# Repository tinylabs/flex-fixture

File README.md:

## flex-fixture
Oscilloscope fixture to ease in simple probing without causing undue mess on the workspace. It allows me to more quickly switch between projects and to clean up after by moving the probe boom out of the way. In addition each probe can be plugged directly into Saleae Pro 8 for logic analysis.

### COTS Components
* [Boom microphone mount](https://www.amazon.com/gp/product/B07V2FJL54/ref=ppx_yo_dt_b_asin_title_o07_s00?ie=UTF8&psc=1)
* [5/8 to 3/8" adapter](https://www.amazon.com/Donuts-Adapter-Female-Knurled-Microphone/dp/B08VGTCZWN)
* [Magnetic mount PCB holder + flex arms](https://www.aliexpress.us/item/2251832832414460.html)
* [P100 pogo pins](https://www.amazon.com/gp/product/B017N4Y79U)
* [P100 pogo pins](https://www.amazon.com/gp/product/B018HMJKRG)
* [P100 pogo pin receptacle](https://www.amazon.com/Spring-Probe-Sleeve-Accessory-R125%E2%80%914s/dp/B0B6PNLFZ7)
* [CONBNC002](https://www.mouser.com/ProductDetail/Linx-Technologies/CONBNC002)
* Probe to BNC adapter (typically included with oscope probes)
* Twisted pair wire from CAT5 cable
* Zip ties to mount o-scope probe to probe mount
* M5 screws to mount probe mount to boom mount
* M4 screws to mount PCBs to 3d printed parts
* M4/M5 tap for 3d printed parts
* Recommended resin is Sirayatech blu

### 3D printed parts
* Boom mount
* Oscilloscope probe attachment (1 per channel)
* Flex arm mount

### PCBs (combined with mouse bite)
* Probe -> BNC -> 0.1" conversion
* Pogo pin -> 0.1"

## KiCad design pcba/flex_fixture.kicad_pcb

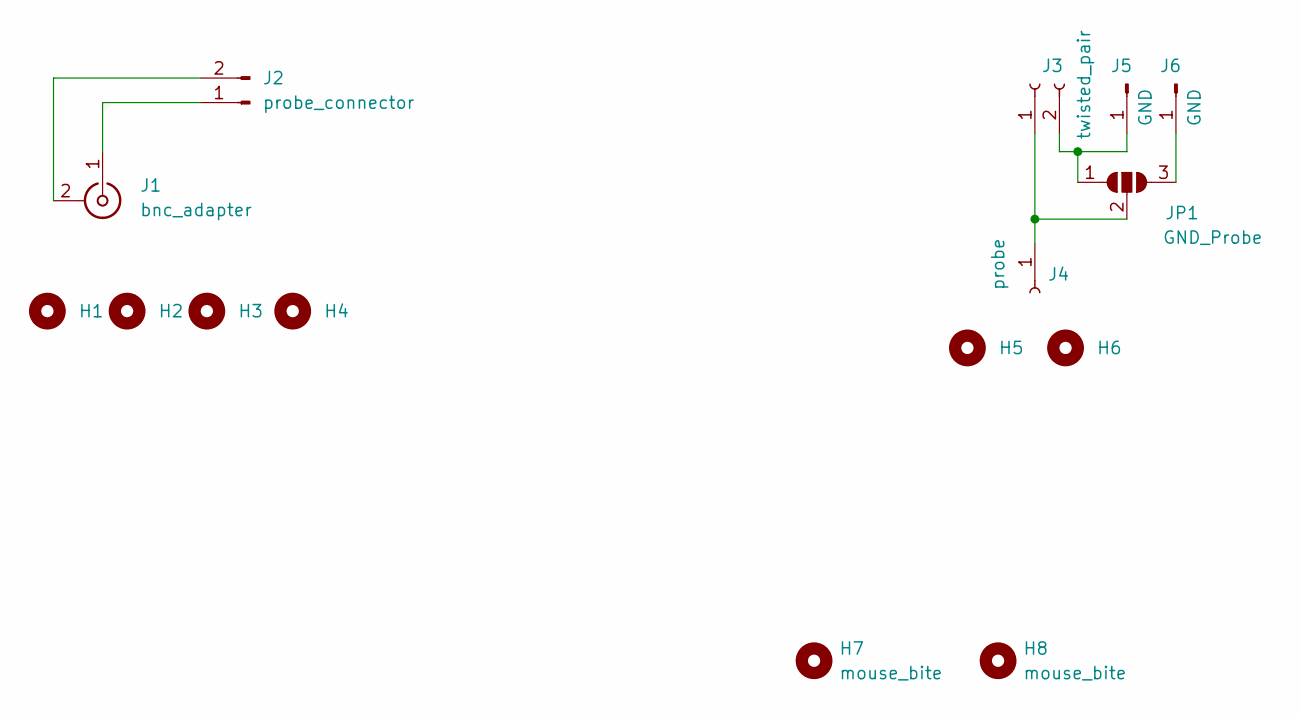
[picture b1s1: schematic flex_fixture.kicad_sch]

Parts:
H1, H2, H3, H4, H5, H6: MountingHole; MountingHole_4.3mm_M4
H7, H8: mouse_bite; mouse-bite-3mm-slot
J1: bnc_adapter; CONBNC002
J2: probe_connector; PinHeader_1x02_P2.54mm_Horizontal
J3: twisted_pair; PinSocket_1x02_P2.54mm_Horizontal
J4: probe; PinSocket_1x01_P2.54mm_Horizontal
J5, J6: GND; PinSocket_1x01_P2.54mm_Horizontal
JP1: GND_Probe; SolderJumper-3_P1.3mm_Open_RoundedPad1.0x1.5mm

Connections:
unnamed: J1.1 (In), J2.1
unnamed: J1.2 (Ext), J2.2
unnamed: J3.1, J4.1, JP1.2 (C)
unnamed: J3.2, J5.1, JP1.1 (A)
unnamed: J6.1, JP1.3 (B)

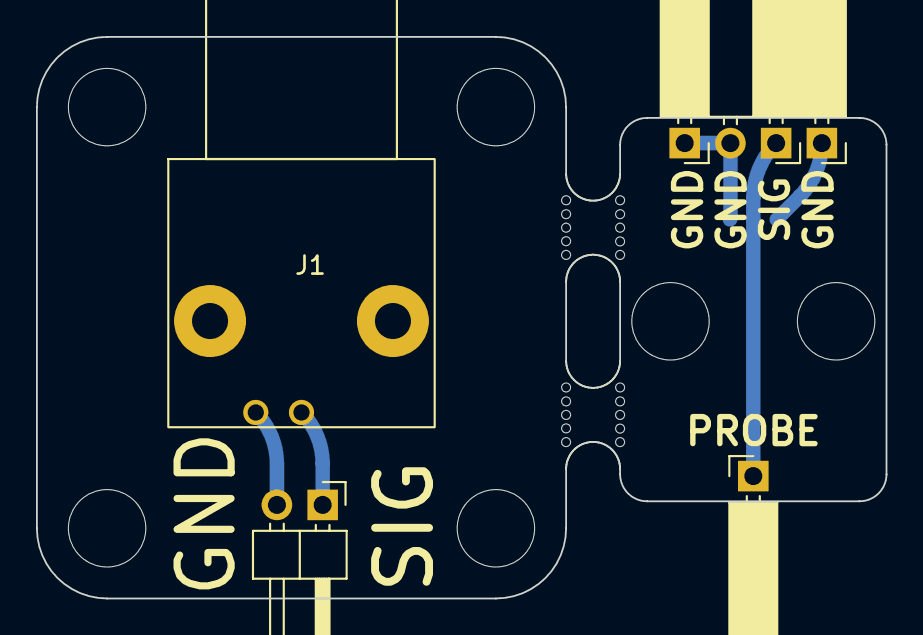
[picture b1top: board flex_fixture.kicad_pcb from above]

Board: 2 copper layers, 47.2 x 31.2 mm, 15 parts (1 on the bottom side), 5 nets.

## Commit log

2023-03-08 Initial checkin
2023-03-08 Add screenshot
2023-03-08 Add saleae logic pro holder
2023-03-09 Update probe and saleae dimensions
2023-03-09 Add STLs
2023-03-13 Add footprints
